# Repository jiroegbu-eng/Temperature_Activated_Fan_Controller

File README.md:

# Temperature-Activated Fan Controller

A 12V fan controller circuit designed in KiCad. The board turns a cooling fan on or off based on temperature using a 10k NTC thermistor, an LM358 comparator, and an IRLIZ44N MOSFET.

This project is part of my electronics design portfolio. The focus was on building a practical thermal management circuit with a clean schematic, routed PCB layout, and proper ERC/DRC verification.

## Project Summary

The circuit senses temperature through an NTC thermistor voltage divider. A 10k potentiometer sets the fan turn-on threshold. The LM358 compares the thermistor voltage against the threshold voltage, then drives the MOSFET gate when the fan should turn on.

The fan is switched using a low-side MOSFET arrangement. The fan positive terminal is tied to +12V, while the MOSFET controls the ground side of the fan. A 1N4007 diode is placed across the fan output to protect the MOSFET from voltage spikes when the fan turns off.

## Why I Built This

This project is more practical than a simple light sensor circuit because thermal control is common in real electronics systems. Power supplies, motor drivers, amplifiers, embedded boards, and battery systems often need basic fan control or thermal protection.

The project demonstrates:

* Analog sensor interfacing
* Comparator-based switching
* Adjustable threshold control
* Hysteresis feedback
* MOSFET load switching
* Inductive load protection
* PCB layout for power and signal separation

## Main Specifications

| Item               | Detail                        |
| ------------------ | ----------------------------- |
| Supply voltage     | 12V DC                        |
| Temperature sensor | 10k NTC thermistor @ 25°C     |
| Comparator         | LM358                         |
| Switching device   | IRLIZ44N N-channel MOSFET     |
| Fan control method | Low-side switching            |
| PCB type           | 2-layer PCB                   |
| Design software    | KiCad 10.0.1                  |
| Simulation         | Not included for this project |

## Circuit Operation

The NTC thermistor and a 10k resistor form a voltage divider. As temperature changes, the resistance of the thermistor changes, which also changes the voltage at the `TEMP_SENSE` node.

The 10k potentiometer creates an adjustable reference voltage called `REF_SET`. This lets the fan turn-on point be tuned manually.

The LM358 compares `TEMP_SENSE` against `REF_SET`. When the sensed temperature crosses the set threshold, the LM358 output changes state and drives the MOSFET gate through a 100Ω gate resistor.

The MOSFET switches the fan on the low side. This means the fan receives +12V directly, while the MOSFET connects or disconnects the fan’s ground path.

A 100k resistor provides hysteresis feedback from the comparator output back to the sensing node. This helps stop the fan from rapidly switching on and off when the temperature is close to the threshold.

## Key Design Choices

### NTC Thermistor Divider

The 10k NTC thermistor was paired with a 10k resistor to create a simple temperature-dependent voltage divider. Using equal nominal values around room temperature gives a useful mid-range voltage for the comparator input.

### Adjustable Threshold

A 10k potentiometer was used so the fan turn-on point can be adjusted without changing resistor values. This makes the circuit more flexible and easier to tune.

### Hysteresis Resistor

A 100k feedback resistor was added between the LM358 output and the temperature sensing node. This creates a small amount of hysteresis, which prevents fan chatter around the switching point.

### MOSFET Switching

The IRLIZ44N was selected because it is suitable for low-side switching of 12V fan loads and can be driven from a logic-level control signal. The MOSFET handles the fan current while the LM358 only drives the gate.

### Flyback Protection

The 1N4007 diode is placed across the fan output. Since a fan is an inductive load, it can produce a voltage spike when switched off. The diode gives that energy a safe path and protects the MOSFET.

### PCB Layout

The high-current fan path was routed with wider traces. The low-current sensor and comparator traces were routed separately using smaller traces. The thermistor was placed away from the MOSFET and fan output area to reduce unwanted heating and noise coupling.

## Main Components

| Reference | Component                  | Value / Part         |
| --------- | -------------------------- | -------------------- |
| U1        | Op-amp / comparator        | LM358                |
| Q1        | N-channel MOSFET           | IRLIZ44N             |
| RT1       | NTC thermistor             | 10k @ 25°C           |
| RV1       | Potentiometer              | 10k                  |
| R1        | Divider resistor           | 10k                  |
| R2        | Hysteresis resistor        | 100k                 |
| R3        | Gate resistor              | 100Ω                 |
| R4        | Gate pulldown resistor     | 100k                 |
| R5        | LED current-limit resistor | 2.2k                 |
| D1        | Flyback diode              | 1N4007               |
| D2        | Power indicator LED        | LED                  |
| C1        | Decoupling capacitor       | 100nF                |
| C2        | Bulk capacitor             | 10µF                 |
| J1        | Power input connector      | 2-pin screw terminal |
| J2        | Fan output connector       | 2-pin screw terminal |

## Verification

The design was checked in KiCad before finalizing the board.

| Check             | Result   |
| ----------------- | -------- |
| ERC               | 0 errors |
| DRC               | 0 errors |
| Unconnected items | 0        |

## Project Images

### Schematic

### ERC Result

### PCB Layout

### DRC Result

### 3D View

## Repository Structure

```text
Temperature_Activated_Fan_Controller/
├── README.md
├── hardware/
│   ├── Temperature_Activated_Fan_Controller.kicad_pro
│   ├── Temperature_Activated_Fan_Controller.kicad_sch
│   ├── Temperature_Activated_Fan_Controller.kicad_pcb
│   └── Temperature_Activated_Fan_Controller.kicad_prl
├── images/
│   ├── schematic.png
│   ├── erc_0_errors.png
│   ├── pcb_layout.png
│   ├── drc_0_errors.png
│   └── 3d_view.png
└── docs/
    └── bom.md
```

## Tools Used

* KiCad 10.0.1
* KiCad Schematic Editor
* KiCad PCB Editor
* KiCad 3D Viewer

## Status

Completed.

* Schematic finished
* PCB layout finished
* ERC passed with 0 errors
* DRC passed with 0 errors
* 3D board preview generated

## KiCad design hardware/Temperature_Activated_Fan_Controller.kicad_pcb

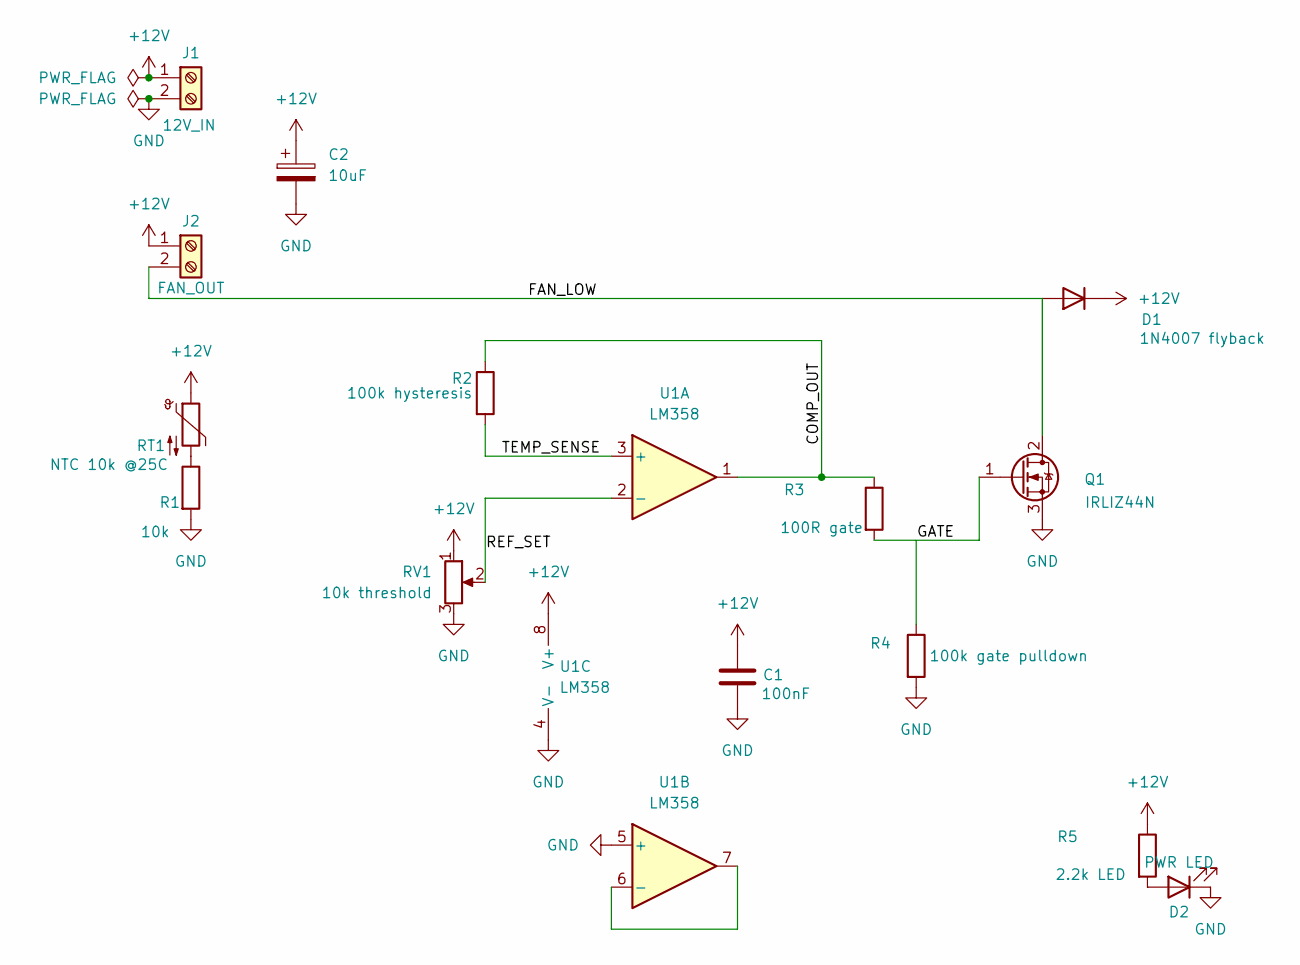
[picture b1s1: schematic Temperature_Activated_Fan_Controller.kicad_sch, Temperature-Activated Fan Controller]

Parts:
C1: 100nF; C_Disc_D3.0mm_W1.6mm_P2.50mm
C2: 10uF; CP_Radial_D5.0mm_P2.50mm
D1: 1N4007 flyback; D_DO-41_SOD81_P10.16mm_Horizontal
D2: PWR LED; LED_D5.0mm
J1: 12V_IN; TerminalBlock_Phoenix_MKDS-1,5-2-5.08_1x02_P5.08mm_Horizont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
J2: FAN_OUT; TerminalBlock_Phoenix_MKDS-1,5-2-5.08_1x02_P5.08mm_Horizont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
Q1: IRLIZ44N; TO-220-3_Vertical
R1: 10k; R_Axial_DIN0207_L6.3mm_D2.5mm_P7.62mm_Horizontal
R2: 100k hysteresis; R_Axial_DIN0207_L6.3mm_D2.5mm_P7.62mm_Horizontal
R3: 100R gate; R_Axial_DIN0207_L6.3mm_D2.5mm_P7.62mm_Horizontal
R4: 100k gate pulldown; R_Axial_DIN0207_L6.3mm_D2.5mm_P7.62mm_Horizontal
R5: 2.2k LED; R_Axial_DIN0207_L6.3mm_D2.5mm_P7.62mm_Horizontal
RT1: NTC 10k @25C; R_Axial_DIN0207_L6.3mm_D2.5mm_P7.62mm_Horizontal
RV1: 10k threshold; Potentiometer_Bourns_3386P_Vertical
U1: LM358; DIP-8_W7.62mm

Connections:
+12V: C1.1, C2.1, D1.1 (K), J1.1, J2.1, R5.1, RT1.1, RV1.1, U1.8 (V+)
/COMP_OUT: R2.1, R3.1, U1.1
/FAN_LOW: D1.2 (A), J2.2, Q1.2 (D)
/GATE: Q1.1 (G), R3.2, R4.1
/REF_SET: RV1.2, U1.2 (-)
/TEMP_SENSE: R2.2, U1.3 (+)
GND: C1.2, C2.2, D2.1 (K), J1.2, Q1.3 (S), R1.2, R4.2, RV1.3, U1.4 (V-), U1.5 (+)
unnamed: D2.2 (A), R5.2
unnamed: R1.1, RT1.2
unnamed: U1.6 (-), U1.7

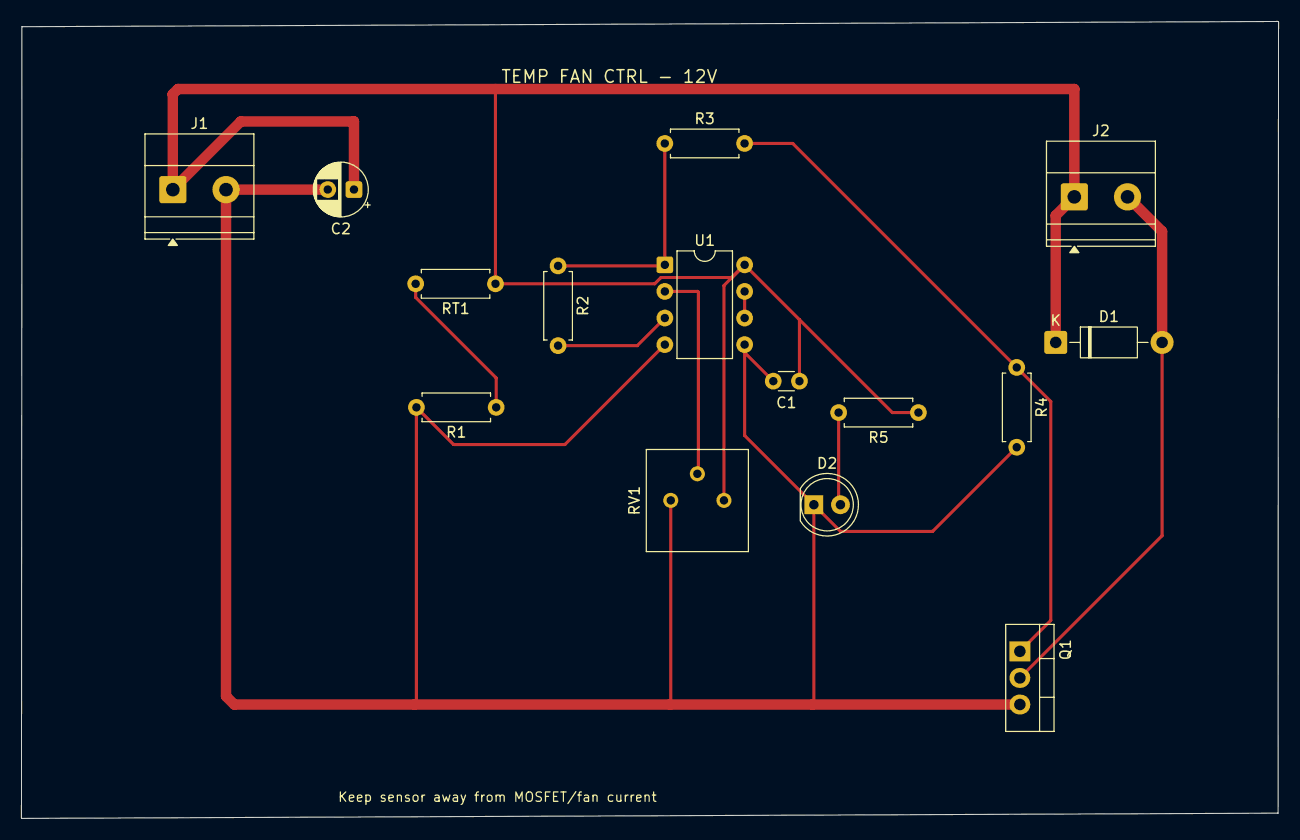
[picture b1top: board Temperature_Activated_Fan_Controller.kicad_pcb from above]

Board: 2 copper layers, 120.0 x 76.1 mm, 15 parts (0 on the bottom side), 10 nets.

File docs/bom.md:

# Bill of Materials

| Reference | Component                | Value / Part         | Package / Footprint Used                           | Purpose / Notes                                                                                                                                                                               |
| --------- | ------------------------ | -------------------- | -------------------------------------------------- | --------------------------------------------------------------------------------------------------------------------------------------------------------------------------------------------- |
| U1        | Dual op-amp / comparator | LM358                | DIP-8                                              | Used as the comparator. One op-amp section compares the thermistor voltage with the adjustable threshold voltage. The unused second op-amp section is tied off properly so it does not float. |
| Q1        | N-channel MOSFET         | IRLIZ44N             | TO-220-3 vertical                                  | Low-side switch for the 12V fan. The MOSFET handles the fan current while the LM358 only drives the gate.                                                                                     |
| RT1       | NTC thermistor           | 10k @ 25°C           | Through-hole thermistor / resistor-style footprint | Temperature sensor. Its resistance decreases as temperature rises, changing the `TEMP_SENSE` voltage.                                                                                         |
| RV1       | Potentiometer            | 10k                  | Bourns 3386P vertical trimmer footprint            | Sets the adjustable temperature threshold. Turning the potentiometer changes the `REF_SET` voltage going into the LM358.                                                                      |
| R1        | Resistor                 | 10k                  | Axial through-hole resistor                        | Forms the lower half of the thermistor voltage divider with RT1.                                                                                                                              |
| R2        | Resistor                 | 100k                 | Axial through-hole resistor                        | Hysteresis feedback resistor from the LM358 output back to the temperature sense input. Helps prevent fan chatter near the switching point.                                                   |
| R3        | Resistor                 | 100Ω                 | Axial through-hole resistor                        | MOSFET gate resistor. Limits sudden gate charging current and helps keep the gate drive stable.                                                                                               |
| R4        | Resistor                 | 100k                 | Axial through-hole resistor                        | MOSFET gate pulldown resistor. Keeps the MOSFET off when the comparator output is inactive or during startup.                                                                                 |
| R5        | Resistor                 | 2.2k                 | Axial through-hole resistor                        | Current-limiting resistor for the power indicator LED.                                                                                                                                        |
| D1        | Rectifier diode          | 1N4007               | DO-41 through-hole diode                           | Flyback diode across the fan output. Protects the MOSFET from voltage spikes when the fan motor switches off.                                                                                 |
| D2        | LED                      | Power indicator LED  | 5mm through-hole LED                               | Turns on when the board receives power. Used as a simple power status indicator.                                                                                                              |
| C1        | Ceramic capacitor        | 100nF                | Through-hole disc capacitor                        | LM358 decoupling capacitor. Helps reduce small supply noise close to the op-amp power pins.                                                                                                   |
| C2        | Electrolytic capacitor   | 10µF                 | Radial through-hole capacitor                      | Bulk input capacitor across the 12V supply. Helps stabilize the input rail when the fan switches.                                                                                             |
| J1        | Screw terminal connector | 2-pin terminal block | 5.08mm pitch through-hole terminal block           | 12V DC power input connector. Pin 1 is +12V and pin 2 is GND.                                                                                                                                 |
| J2        | Screw terminal connector | 2-pin terminal block | 5.08mm pitch through-hole terminal block           | Fan output connector. Pin 1 connects to +12V and pin 2 connects to `FAN_LOW`, which is switched by the MOSFET.                                                                                |

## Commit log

2026-06-16 Add final project and verification screenshots
2026-06-16 Add KiCad schematic, PCB layout for fan controller
2026-06-16 Add detailed BOM document
2026-06-16 Add design rationale
2026-06-16 Complete temperature-activated fan controller project
